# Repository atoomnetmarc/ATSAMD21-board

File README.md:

# ATSAMD21 board

This is a pcb I designed in 2014 to breakout a ATSAMD21 to some headers.

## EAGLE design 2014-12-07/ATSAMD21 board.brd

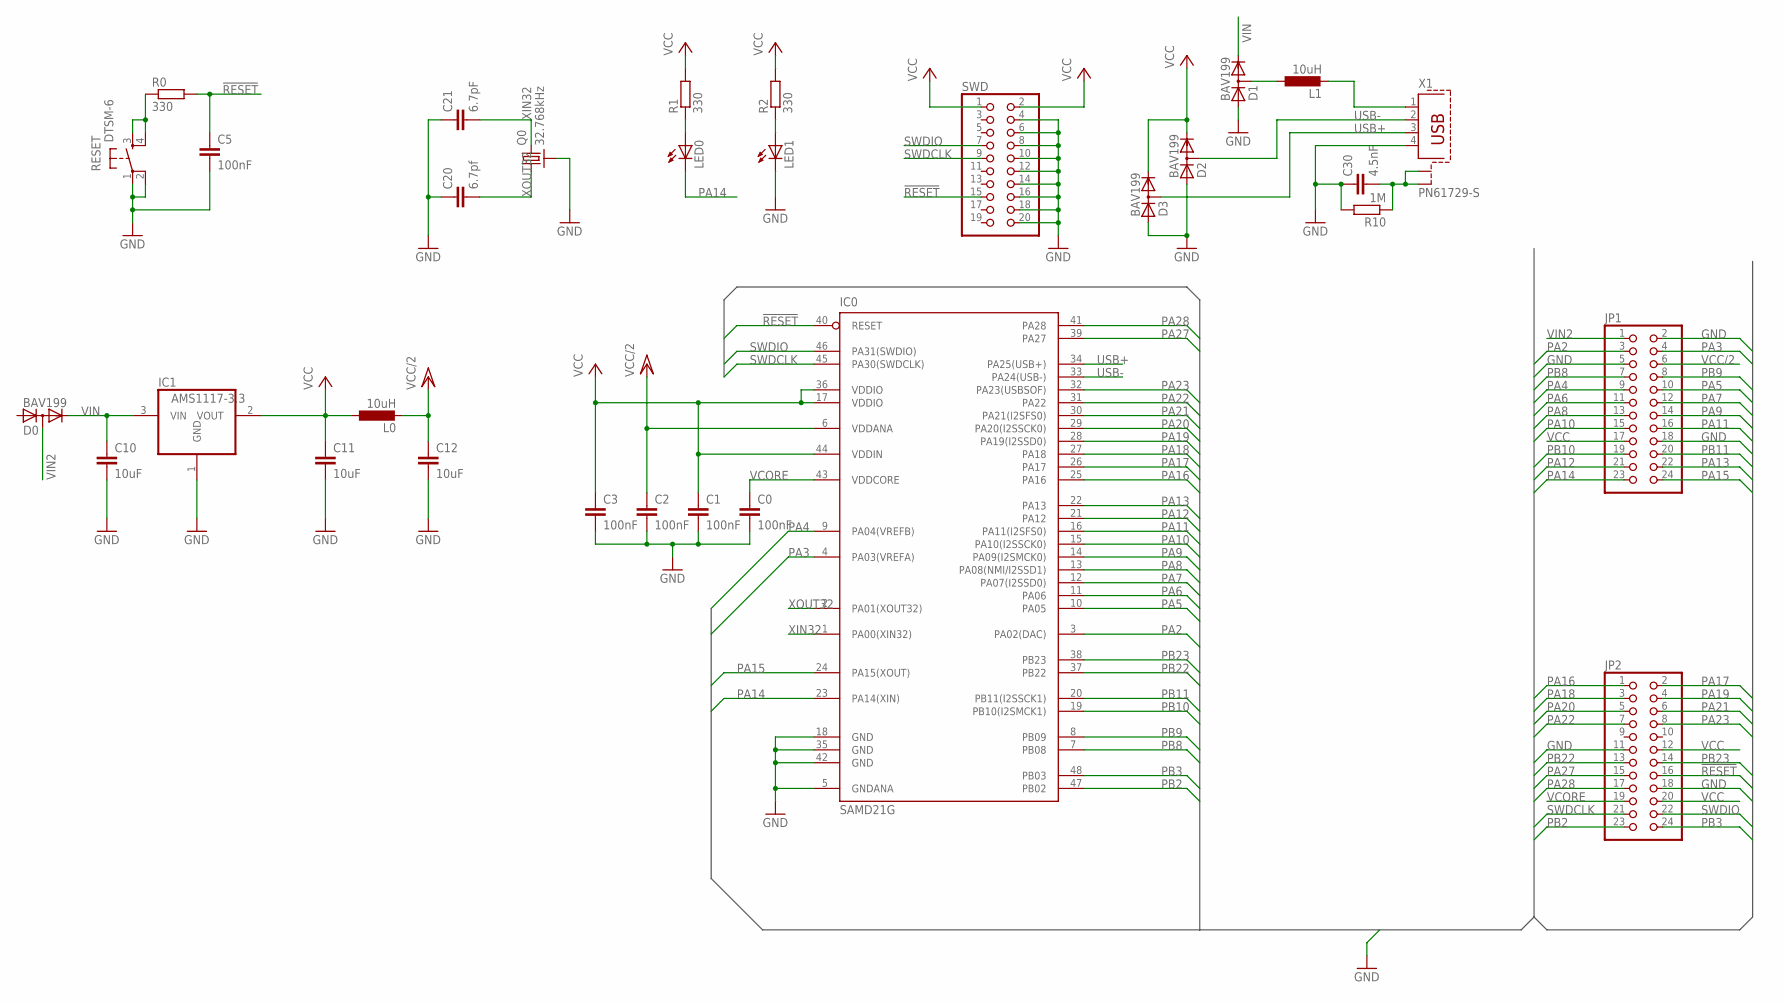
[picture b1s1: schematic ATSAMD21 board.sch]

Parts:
C0, C1, C2, C3, C5: 100nF; C0805K
C10, C11, C12: 10uF; C0805K
C20: 6.7pf; C0805K
C21: 6.7pF; C0805K
C30: 4.5nF; C0805K
D0, D1, D2, D3: BAV199; SOT23
IC0: SAMD21G; TQFP48
IC1: AMS1117-3.3; SOT223
JP1, JP2: PINHD-2X12; 2X12
L0, L1: 10uH; L2012C
LED0, LED1: LEDCHIP-LED0805; CHIP-LED0805
Q0: 32.768kHz; TC26H
R0, R1, R2: 330; R0805
R10: 1M; R0805
RESET: DTSM-6
SWD: PINHD-2X10; 2X10
X1: PN61729-S

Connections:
!RESET: C5.1, IC0.40 (RESET), JP2.16, R0.2, SWD.15
GND: C0.2, C1.2, C2.2, C3.2, C5.2, C10.2, C11.2, C12.2, C20.1, C21.1, C30.1, D1.1 (A), D2.1 (A), D3.1 (A), IC0.5 (GNDANA), IC0.18 (GND), IC0.35 (GND), IC0.42 (GND), IC1.1 (GND), JP1.2, JP1.5, JP1.18, JP2.11, JP2.18, LED1.C, Q0.P$1 (3), R10.2, RESET.1, RESET.2, SWD.4, SWD.6, SWD.8, SWD.10, SWD.12, SWD.14, SWD.16, SWD.18, SWD.20, X1.4
unnamed: C30.2, R10.1, X1.S1, X1.S2
unnamed: R0.1, RESET.3, RESET.4
unnamed: L1.2, X1.1
unnamed: D1.3 (AC), L1.1
unnamed: LED0.A, R1.1
unnamed: LED1.A, R2.1
PA2: IC0.3 (PA02(DAC)), JP1.3
PA3: IC0.4 (PA03(VREFA)), JP1.4
PA4: IC0.9 (PA04(VREFB)), JP1.9
PA5: IC0.10 (PA05), JP1.10
PA6: IC0.11 (PA06), JP1.11
PA7: IC0.12 (PA07(I2SSD0)), JP1.12
PA8: IC0.13 (PA08(NMI/I2SSD1)), JP1.13
PA9: IC0.14 (PA09(I2SMCK0)), JP1.14
PA10: IC0.15 (PA10(I2SSCK0)), JP1.15
PA11: IC0.16 (PA11(I2SFS0)), JP1.16
PA12: IC0.21 (PA12), JP1.21
PA13: IC0.22 (PA13), JP1.22
PA14: IC0.23 (PA14(XIN)), JP1.23, LED0.C
PA15: IC0.24 (PA15(XOUT)), JP1.24
PA16: IC0.25 (PA16), JP2.1
PA17: IC0.26 (PA17), JP2.2
PA18: IC0.27 (PA18), JP2.3
PA19: IC0.28 (PA19(I2SSD0)), JP2.4
PA20: IC0.29 (PA20(I2SSCK0)), JP2.5
PA21: IC0.30 (PA21(I2SFS0)), JP2.6
PA22: IC0.31 (PA22), JP2.7
PA23: IC0.32 (PA23(USBSOF)), JP2.8
PA27: IC0.39 (PA27), JP2.15
PA28: IC0.41 (PA28), JP2.17
PB2: IC0.47 (PB02), JP2.23
PB3: IC0.48 (PB03), JP2.24
PB8: IC0.7 (PB08), JP1.7
PB9: IC0.8 (PB09), JP1.8
PB10: IC0.19 (PB10(I2SMCK1)), JP1.19
PB11: IC0.20 (PB11(I2SSCK1)), JP1.20
PB22: IC0.37 (PB22), JP2.13
PB23: IC0.38 (PB23), JP2.14
SWDCLK: IC0.45 (PA30(SWDCLK)), JP2.21, SWD.9
SWDIO: IC0.46 (PA31(SWDIO)), JP2.22, SWD.7
USB+: D3.3 (AC), IC0.34 (PA25(USB+)), X1.3
USB-: D2.3 (AC), IC0.33 (PA24(USB-)), X1.2
VCC: C1.1, C3.1, C11.1, D2.2 (C), D3.2 (C), IC0.17 (VDDIO), IC0.36 (VDDIO), IC0.44 (VDDIN), IC1.2 (VOUT), JP1.17, JP2.12, JP2.20, L0.1, R1.2, R2.2, SWD.1, SWD.2
VCC/2: C2.1, C12.1, IC0.6 (VDDANA), JP1.6, L0.2
VCORE: C0.1, IC0.43 (VDDCORE), JP2.19
VIN: C10.1, D0.2 (C), D1.2 (C), IC1.3 (VIN)
VIN2: D0.3 (AC), JP1.1
XIN32: C21.2, IC0.1 (PA00(XIN32)), Q0.2
XOUT32: C20.2, IC0.2 (PA01(XOUT32)), Q0.1

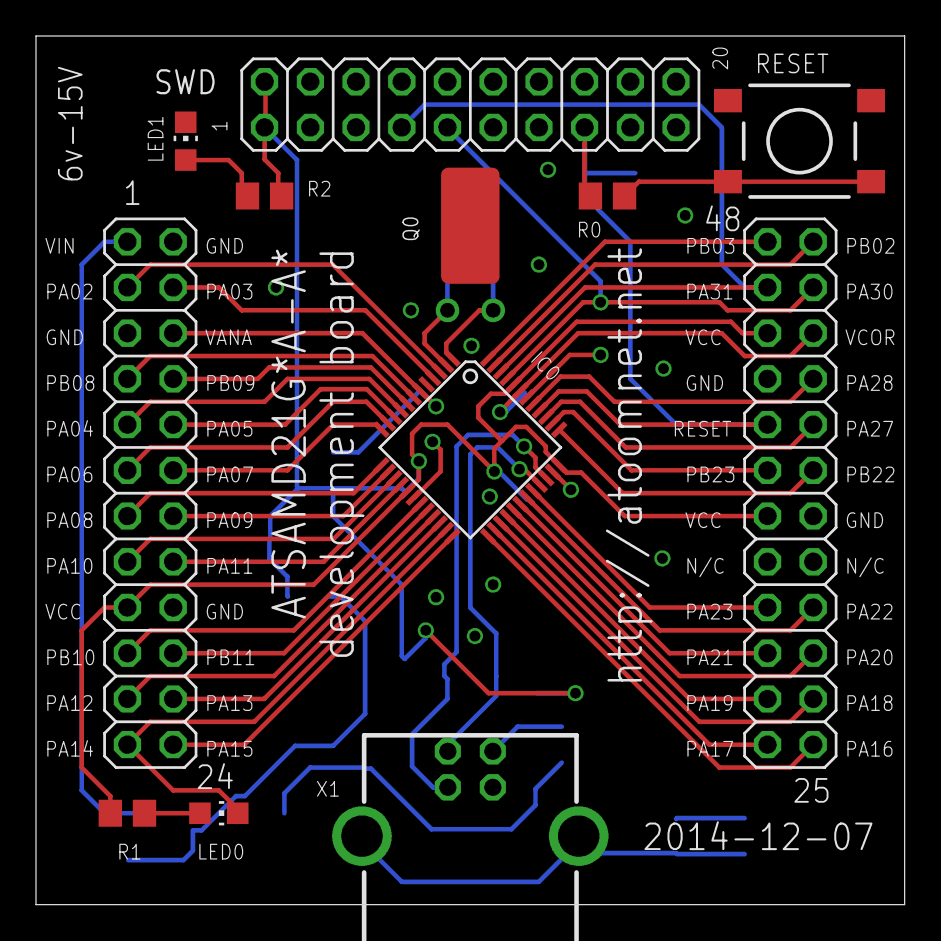
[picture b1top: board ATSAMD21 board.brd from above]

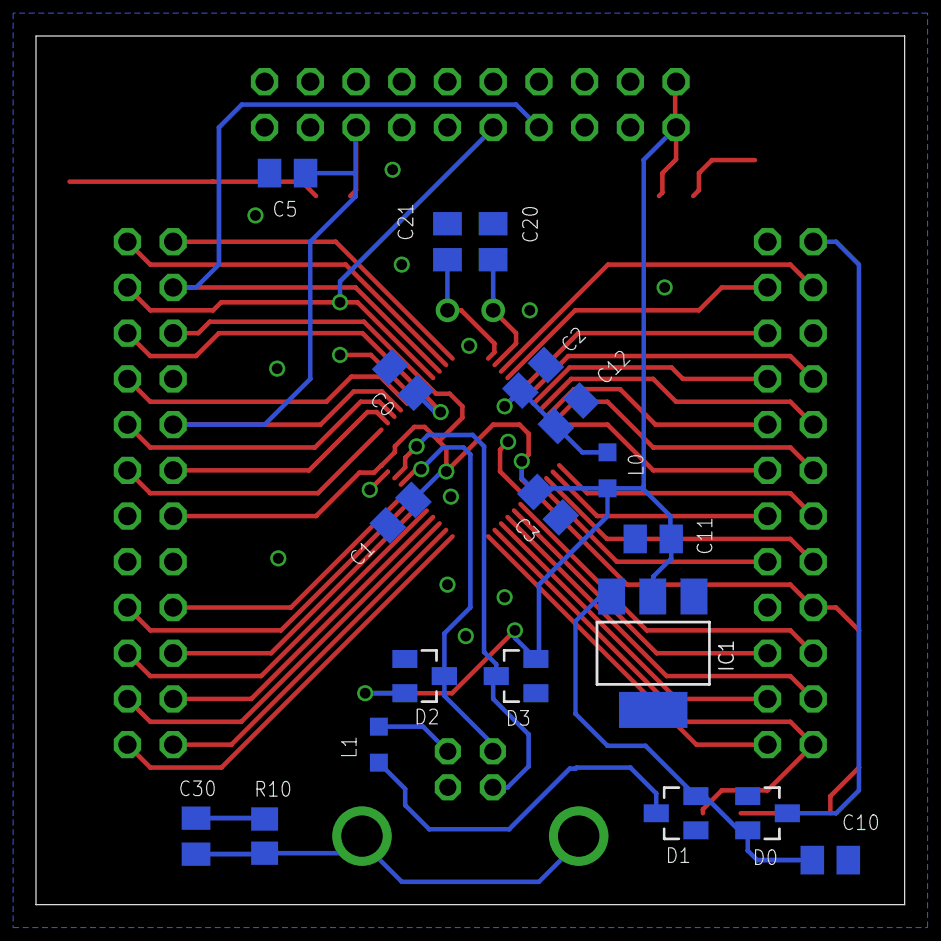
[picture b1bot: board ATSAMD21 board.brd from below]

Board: 2 copper layers, 48.3 x 48.3 mm, 31 parts (19 on the bottom side), 51 nets.

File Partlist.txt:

Partlist

Exported from ATSAMD21 board.sch at 23-12-2014 10:40:27

EAGLE Version 7.1.0 Copyright (c) 1988-2014 CadSoft

Assembly variant: 

Part     Value          Device          Package      Library     Sheet

C0       100nF          C-EUC0805K      C0805K       rcl         1
C1       100nF          C-EUC0805K      C0805K       rcl         1
C2       100nF          C-EUC0805K      C0805K       rcl         1
C3       100nF          C-EUC0805K      C0805K       rcl         1
C5       100nF          C-EUC0805K      C0805K       rcl         1
C10      10uF           C-EUC0805K      C0805K       rcl         1
C11      10uF           C-EUC0805K      C0805K       rcl         1
C12      10uF           C-EUC0805K      C0805K       rcl         1
C20      6.7pf          C-EUC0805K      C0805K       rcl         1
C21      6.7pF          C-EUC0805K      C0805K       rcl         1
C30      4.5nF          C-EUC0805K      C0805K       rcl         1
D0       BAV199         BAV199          SOT23        diode       1
D1       BAV199         BAV199          SOT23        diode       1
D2       BAV199         BAV199          SOT23        diode       1
D3       BAV199         BAV199          SOT23        diode       1
IC0      SAMD21G        SAMD21G         TQFP48       atsamd21    1
IC1      AMS1117-3.3    REG1117         SOT223       burr-brown  1
JP1                     PINHD-2X12      2X12         pinhead     1
JP2                     PINHD-2X12      2X12         pinhead     1
L0       10uH           L-EUL2012C      L2012C       rcl         1
L1       10uH           L-EUL2012C      L2012C       rcl         1
LED0                    LEDCHIP-LED0805 CHIP-LED0805 led         1
LED1                    LEDCHIP-LED0805 CHIP-LED0805 led         1
Q0       32.768kHz      CRYSTALTC26H    TC26H        crystal     1
R0       330            R-EU_R0805      R0805        rcl         1
R1       330            R-EU_R0805      R0805        rcl         1
R2       330            R-EU_R0805      R0805        rcl         1
R10      1M             R-EU_R0805      R0805        rcl         1
RESET    DTSM-6         DTSM-6          DTSM-6       switch-tact 1
SWD                     PINHD-2X10      2X10         pinhead     1
X1       PN61729-S      PN61729-S       PN61729-S    usb-conn    1

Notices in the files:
README.md:
License: Apache 2.0
